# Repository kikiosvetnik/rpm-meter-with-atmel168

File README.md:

# rpm-meter-with-atmel168
Initial idea was to make RPM meter for my car which then outputs RPM on LEDs.
I decided to take signal directly from one of four coils in order to get rotation per minute, and then output it on Addressable LEDs WS2812B.
One button is for reset of MCU & other two are for user interface, idea is to be able to change rpm at which LED start to light, and color if each individual LED.
### Update:
 Additionally I've added 8 outputs for regulars LEDs and Input to ADC with Resistor for Temperature sensing(NTC) per request from my friend to make RPM instrument "shine" in his old BMW E34 as it shined in M5 from that age.

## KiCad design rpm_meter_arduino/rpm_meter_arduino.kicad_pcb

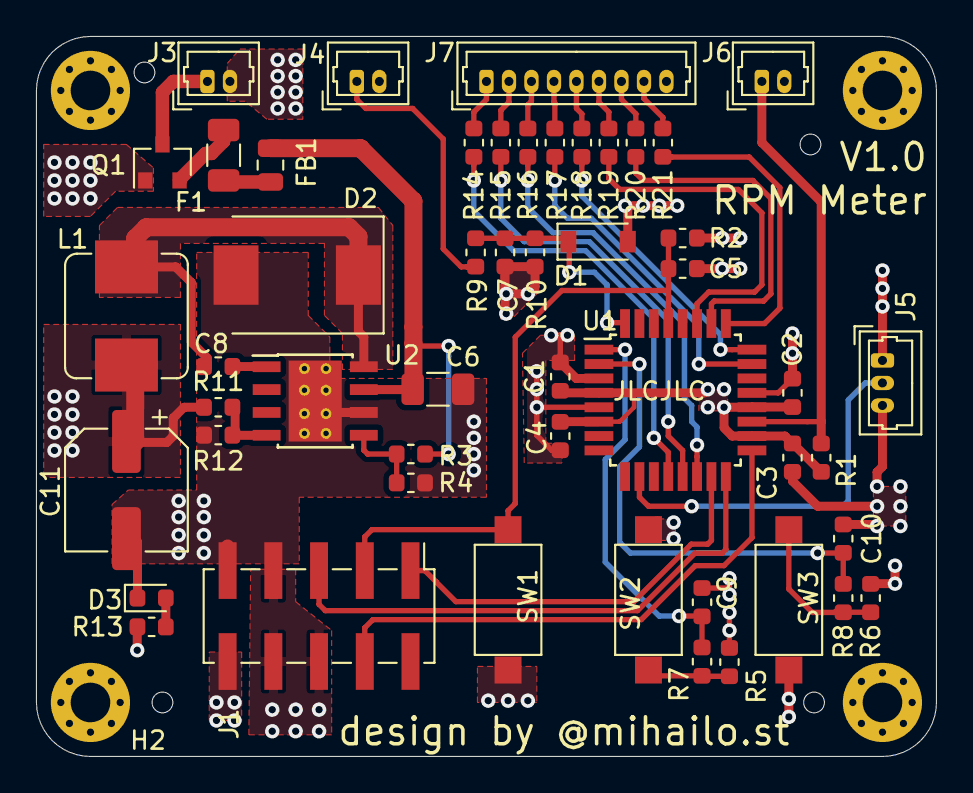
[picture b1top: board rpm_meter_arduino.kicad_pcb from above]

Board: 4 copper layers, 50.0 x 40.0 mm, 54 parts (0 on the bottom side), 39 nets.

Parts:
C1, C2, C3, C4, C5, C9, C10: 100n; C_0603_1608Metric
C6: 10u; C_1206_3216Metric
C7, C8: 10n; C_0603_1608Metric
C11: 220u; CP_Elec_6.3x7.7
D1: 4V7; D_SOD-123
D2: B340; D_SMC
D3: RED; LED_0603_1608Metric
F1: 250mA; Fuse_1206_3216Metric
FB1: 600 @ 600Mhz; L_0805_2012Metric
H1, H2, H3, H4: MountingHole_Pad; MountingHole_2.2mm_M2_Pad_Via
J1: Conn_02x05_Counter_Clockwise; PinHeader_2x05_P2.54mm_Vertical_SMD
J3, J4, J6: Conn_01x02; Molex_PicoBlade_53047-0210_1x02_P1.25mm_Vertical
J5: Conn_01x03; Molex_PicoBlade_53047-0310_1x03_P1.25mm_Vertical
J7: Conn_01x09; Molex_PicoBlade_53047-0910_1x09_P1.25mm_Vertical
L1: 15uH; L_Bourns_SRP7028A_7.3x6.6mm
Q1: AO3401A; SOT-23
R1: 12K; R_0603_1608Metric
R2, R5, R6, R7, R8: 10K; R_0603_1608Metric
R3: 100K; R_0603_1608Metric
R4: 68K; R_0603_1608Metric
R9, R10: 1K; R_0603_1608Metric
R11: 10k; R_0603_1608Metric
R12: 3k24; R_0603_1608Metric
R13: 680; R_0603_1608Metric
R14, R15, R16, R17, R18, R19, R20, R21: 510; R_0603_1608Metric
SW1: SW_SPST; SW_SPST_CK_RS282G05A3
SW2, SW3: SW_Push; SW_SPST_CK_RS282G05A3
U1: ATmega168-20AU; TQFP-32_7x7mm_P0.8mm
U2: TPS5430DDA; TI_SO-PowerPAD-8_ThermalVias

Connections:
+5V: C1.1, C2.1, C3.1, C4.1, C11.1, J1.10, J5.1, L1.2, R1.1, R2.1, R5.1, R6.1, R11.1, R13.2, U1.4, U1.6, U1.18, U1.20
+12V: J3.1, Q1.3
BUTTON_1: C9.1, R7.1, U1.1
BUTTON_2: C10.1, R8.1, U1.2
GND: C1.2, C2.2, C3.2, C4.2, C5.2, C6.2, C7.2, C9.2, C10.2, C11.2, D1.2, D2.2, D3.1, H1.1, H2.1, H3.1, H4.1, J1.6, J1.7, J1.8, J1.9, J3.2, J4.2, J5.3, J6.2, J7.9, Q1.1, R4.2, R10.2, R12.2, SW1.2, SW2.1, SW3.1, U1.3, U1.5, U1.21, U2.6, U2.9
LED0: R14.2, U1.12
LED1: R15.2, U1.13
LED2: R16.2, U1.14
LED3: R17.2, U1.23
LED4: R18.2, U1.24
LED5: R19.2, U1.27
LED6: R20.2, U1.26
LED7: R21.2, U1.25
MISO: J1.5, U1.16
MOSI: J1.1, U1.15
NTC_A: J6.1, R1.2, U1.19
unnamed: C6.1, FB1.1, R3.1, U2.7
unnamed: C8.1, U2.1
unnamed: C8.2, D2.1, L1.1, U2.8
unnamed: D3.2, R13.1
unnamed: F1.1, FB1.2
unnamed: F1.2, Q1.2
unnamed: J7.1, R14.1
unnamed: J7.2, R15.1
unnamed: J7.3, R16.1
unnamed: J7.4, R17.1
unnamed: J7.5, R18.1
unnamed: J7.6, R19.1
unnamed: J7.7, R20.1
unnamed: J7.8, R21.1
unnamed: R3.2, R4.1, U2.5
unnamed: R5.2, R7.2, SW2.2
unnamed: R6.2, R8.2, SW3.2
unnamed: R11.2, R12.1, U2.4
RESET: C5.1, J1.3, R2.2, SW1.1, U1.29
RGB_Data: J5.2, U1.10
RPM: C7.1, D1.1, R9.2, R10.1, U1.32
RPM_Sense: J4.1, R9.1
SCK: J1.4, U1.17

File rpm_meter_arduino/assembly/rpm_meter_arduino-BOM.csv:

Comment,Designator,Footprint,LCSC
100n,"C1,C2,C3,C4,C5,C9,C10",Capacitor_SMD:C_0603_1608Metric,C14663
220u,C11,Capacitor_SMD:CP_Elec_6.3x7.7,C13585
10u,C6,Capacitor_SMD:C_1206_3216Metric,C84709
10n,"C7,C8",Capacitor_SMD:C_0603_1608Metric,C127968
4V7,D1,Diode_SMD:D_SOD-123,C9995
B340,D2,Diode_SMD:D_SMC,C110486
RED,D3,LED_SMD:LED_0603_1608Metric,C72043
250mA,F1,Fuse:Fuse_1206_3216Metric,C369159
600 @ 600Mhz,FB1,Inductor_SMD:L_0805_2012Metric,C1017
MountingHole_Pad,"H1,H2,H3,H4",MountingHole:MountingHole_2.2mm_M2_Pad_Via,
Conn_02x05_Counter_Clockwise,J1,Connector_PinHeader_2.54mm:PinHeader_2x05_P2.54mm_Vertical_SMD,
Conn_01x02,"J3,J4,J6",Connector_Molex:Molex_PicoBlade_53047-0210_1x02_P1.25mm_Vertical,
Conn_01x03,J5,Connector_Molex:Molex_PicoBlade_53047-0310_1x03_P1.25mm_Vertical,
Conn_01x09,J7,Connector_Molex:Molex_PicoBlade_53047-0910_1x09_P1.25mm_Vertical,
15uH,L1,Inductor_SMD:L_Bourns_SRP7028A_7.3x6.6mm,C132136
AO3401A,Q1,Package_TO_SOT_SMD:SOT-23,C693260
12K,R1,Resistor_SMD:R_0603_1608Metric,C22790
1K,"R9,R10",Resistor_SMD:R_0603_1608Metric,C25804
10k,R11,Resistor_SMD:R_0603_1608Metric,C25803
3k24,R12,Resistor_SMD:R_0603_1608Metric,C23231
680,R13,Resistor_SMD:R_0603_1608Metric,C21190
510,"R14,R15,R16,R17,R18,R19,R20,R21",Resistor_SMD:R_0603_1608Metric,C25804
10K,"R2,R5,R6,R7,R8",Resistor_SMD:R_0603_1608Metric,C22994
100K,R3,Resistor_SMD:R_0603_1608Metric,C23228
68K,R4,Resistor_SMD:R_0603_1608Metric,C23193
SW_SPST,SW1,Button_Switch_SMD:SW_SPST_CK_RS282G05A3,C118141
SW_Push,"SW2,SW3",Button_Switch_SMD:SW_SPST_CK_RS282G05A3,C118141
ATmega168-20AU,U1,Package_QFP:TQFP-32_7x7mm_P0.8mm,C8728
TPS5430DDA,U2,Package_SO:TI_SO-PowerPAD-8_ThermalVias,C9864

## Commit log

2021-04-07 Add files via upload
    Added whole Ki-CAD project. Currently there are few mistakes in BOM list but it will be fixed soon.
2021-04-07 Update README.md
    Added a brief description in readme notes
